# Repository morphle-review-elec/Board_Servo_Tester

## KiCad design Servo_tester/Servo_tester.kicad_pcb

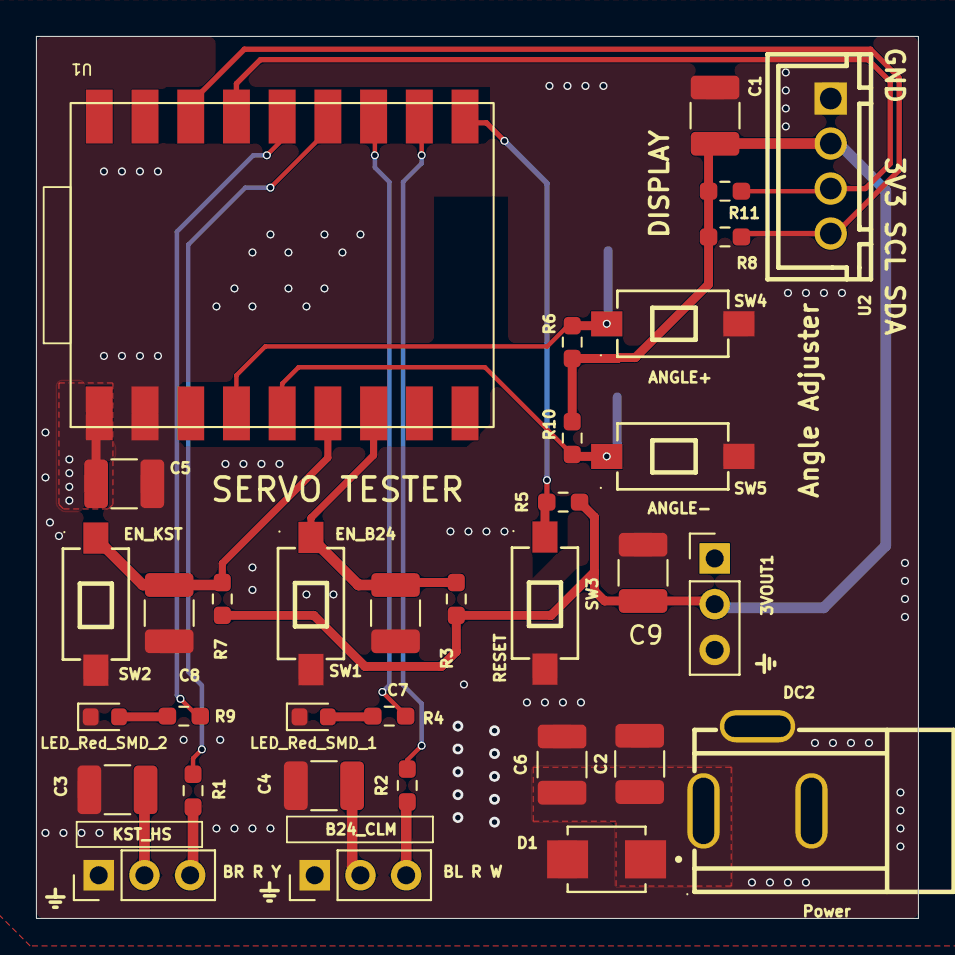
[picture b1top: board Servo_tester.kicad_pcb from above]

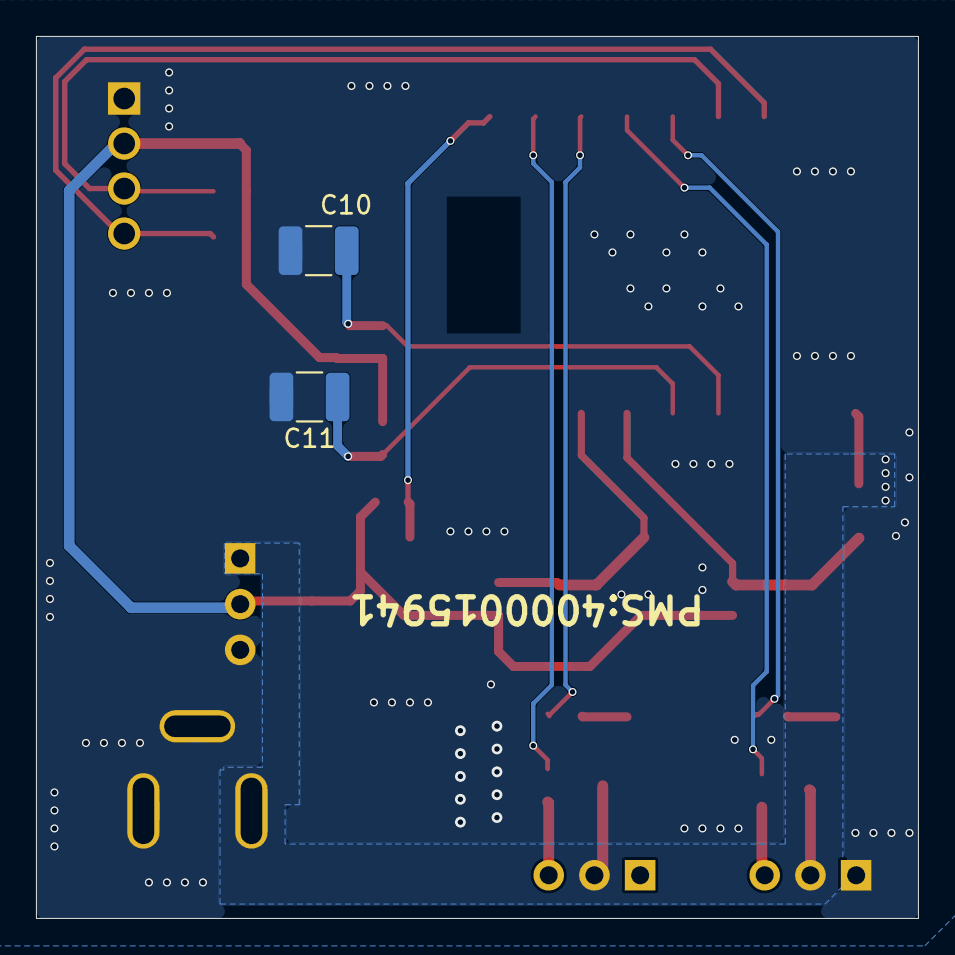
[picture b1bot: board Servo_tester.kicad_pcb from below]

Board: 2 copper layers, 49.0 x 49.0 mm, 36 parts (2 on the bottom side), 18 nets.

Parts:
3VOUT1: 3-Pin_Header; PinHeader_1x03_P2.54mm_Vertical
B24_CLM: 3-Pin_Header; PinHeader_1x03_P2.54mm_Vertical
C1: 0.1uf/1210_3225/16V; C_1210_3225Metric_Pad1.33x2.70mm_HandSolder
C2, C5: 4.7uf/1210_3225/16V; C_1210_3225Metric_Pad1.33x2.70mm_HandSolder
C3, C4, C9: 1uf/1210/16V; C_1210_3225Metric_Pad1.33x2.70mm_HandSolder
C6: 1uf/1210_3225/16V; C_1210_3225Metric_Pad1.33x2.70mm_HandSolder
C7, C8, C10, C11: 100nf/1210/12V; C_1210_3225Metric_Pad1.33x2.70mm_HandSolder
D1: SMBJ5.0A; DIOM4336X265N
DC2: DC-005-2.5A-2.5; CONN-TH_DC-005-2.5A-2.0
KST_HS: 3-Pin_Header; PinHeader_1x03_P2.54mm_Vertical
LED_Red_SMD_1: LED_A; LED_0603_1608Metric
LED_Red_SMD_2: LED_B; LED_0603_1608Metric
R1, R2: 47R; R_0603_1608Metric_Pad0.98x0.95mm_HandSolder
R3, R5, R6, R7, R10: 10K; R_0603_1608Metric_Pad0.98x0.95mm_HandSolder
R4, R9: 1K; R_0603_1608Metric_Pad0.98x0.95mm_HandSolder
R8, R11: 4.7K; R_0603_1608Metric_Pad0.98x0.95mm_HandSolder
SW1, SW2, SW3, SW4, SW5: TSB008A2530A; SW-SMD_L6.0-W3.5-LS8.0
U1: Waveshare-ESP32-C6-Zero
U2: 1.3 Inch I2C OLED; CONN-TH_4P-P2.50_2.54MM-4P-ZZ

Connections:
3V3: 3VOUT1.2, C1.1, C9.1, R3.1, R5.1, R6.1, R7.1, R8.2, R10.1, R11.2, U2.2
ANGLE +: C10.1, R6.2, SW4.1, U1.4 (IO0)
ANGLE −: C11.1, R10.2, SW5.1, U1.5 (IO1)
GND: 3VOUT1.3, B24_CLM.1, C1.2, C2.2, C3.2, C4.2, C5.2, C6.2, C7.2, C8.2, C9.2, C10.2, C11.2, D1.A, DC2.2, DC2.3, KST_HS.1, LED_Red_SMD_1.1 (K), LED_Red_SMD_2.1 (K), SW1.2, SW2.2, SW3.2, SW4.2, SW5.2, U1.2 (GND), U2.1
LED_A: R4.1, U1.12 (IO20)
LED_B: R9.1, U1.14 (IO18)
unnamed: B24_CLM.3, R2.1
unnamed: KST_HS.3, R1.1
unnamed: LED_Red_SMD_1.2 (A), R4.2
unnamed: LED_Red_SMD_2.2 (A), R9.2
PORT_A: C7.1, R3.2, SW1.1, U1.7 (IO3)
PORT_B: C8.1, R7.2, SW2.1, U1.6 (IO2)
RESET: R5.2, SW3.1, U1.10 (IO22)
SCL: R11.1, U1.15 (IO15), U2.3
SDA: R8.1, U1.16 (IO14), U2.4
SERVO A: R2.2, U1.11 (IO21)
SERVO B: R1.2, U1.13 (IO19)
VCC_5V: 3VOUT1.1, B24_CLM.2, C2.1, C3.1, C4.1, C5.1, C6.1, D1.C, DC2.1, KST_HS.2, U1.1 (VCC)

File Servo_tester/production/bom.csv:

Designator,Footprint,Quantity,Value,LCSC Part #
"3VOUT1, B24_CLM, KST_HS",PinHeader_1x03_P2.54mm_Vertical,3,3-Pin_Header,0022232031
C1,1210,1,0.1uf/1210_3225/16V,
"C10, C11, C7, C8",1210,4,100nf/1210/12V,
"C2, C5",1210,2,4.7uf/1210_3225/16V,
"C3, C4, C9",1210,3,1uf/1210/16V,
C6,1210,1,1uf/1210_3225/16V,
D1,DIOM4336X265N,1,SMBJ5.0A,
DC2,CONN-TH_DC-005-2.5A-2.0,1,DC-005-2.5A-2.5,C319098
LED_RED_SMD_1,0603,1,LED_A,
LED_RED_SMD_2,0603,1,LED_B,
"R1, R2",0603,2,47R,
"R10, R3, R5, R6, R7",0603,5,10K,
"R11, R8",0603,2,4.7K,
"R4, R9",0603,2,1K,
"SW1, SW2, SW3, SW4, SW5",SW-SMD_L6.0-W3.5-LS8.0,5,TSB008A2530A,C2888954
U1,Waveshare-ESP32-C6-Zero,1,~,
U2,CONN-TH_4P-P2.50_2.54MM-4P-ZZ,1,1.3 Inch I2C OLED,C5368777
